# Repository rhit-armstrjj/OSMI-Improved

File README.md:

# OSMI-FinalPCB
This is a KiCad 7.0 project. You can install KiCad on Windows with:
1. Open Powershell
2. enter: `winget install KiCad.KiCad`

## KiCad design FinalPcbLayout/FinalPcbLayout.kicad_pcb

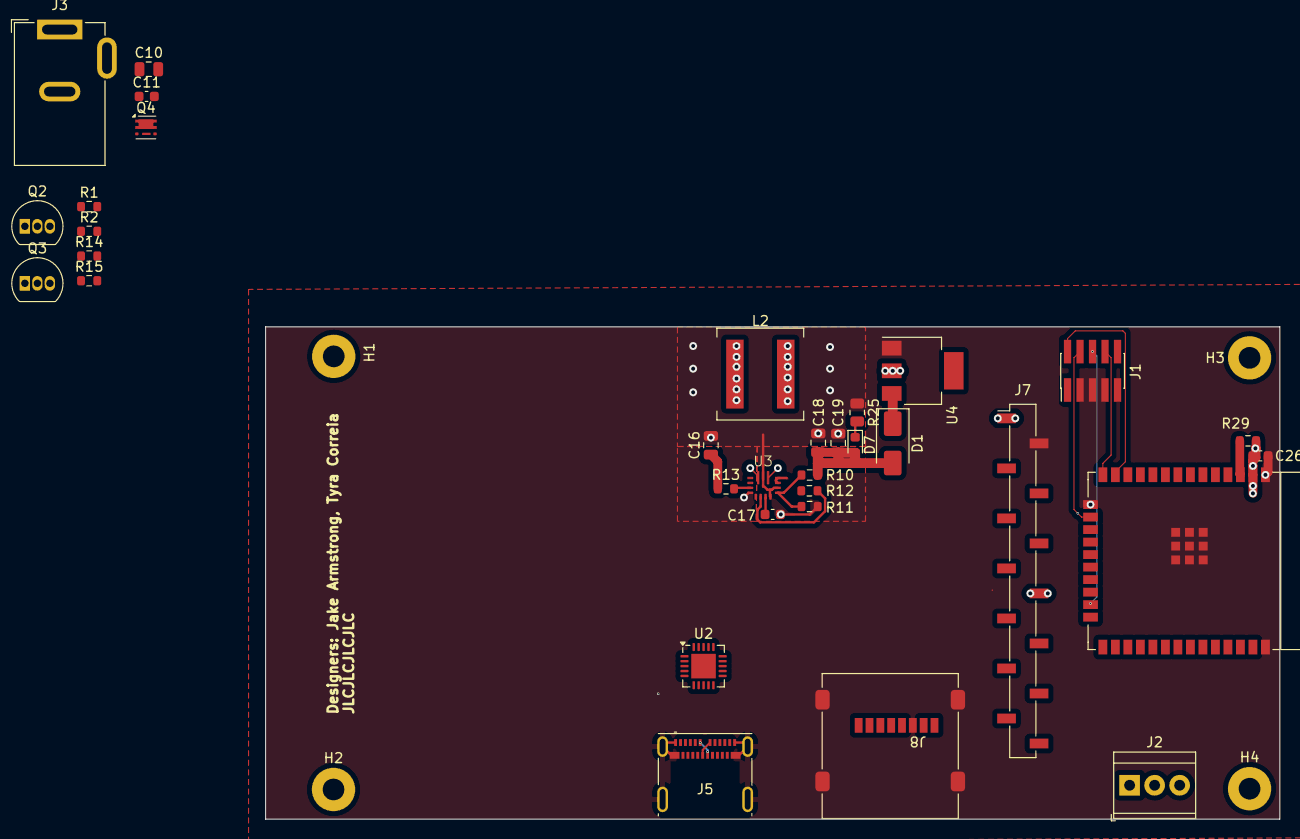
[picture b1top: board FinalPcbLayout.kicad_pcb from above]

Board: 4 copper layers, 103.0 x 50.0 mm, 37 parts (0 on the bottom side), 35 nets.

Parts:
C10, C16, C18: 10uF; C_0805_2012Metric
C11: 22uF; C_0603_1608Metric
C17: 100nF; C_0603_1608Metric
C19: 47uF; C_0805_2012Metric
C26: 0.1uF; C_0603_1608Metric
D1: D_Schottky; D_SMA
D7: RED; LED_0603_1608Metric
H1, H2, H3, H4: MountingHole; MountingHole_2.2mm_M2_Pad
J1: JTAG; PinHeader_2x05_P1.27mm_Vertical_SMD
J2: Conn_01x10; TerminalBlock_TE_282834-3_1x03_P2.54mm_Horizontal
J3: Barrel_Jack; BarrelJack_GCT_DCJ200-10-A_Horizontal
J5: USB_C_Receptacle; USB_C_Receptacle_Molex_105450-0101
J7: Display Socket; PinSocket_1x14_P2.54mm_Vertical_SMD_Pin1Left
J8: Micro_SD_Card; microSD_HC_Molex_47219-2001
L2: 2.2uH; L_Coilcraft_XAL8080-XXX
Q2, Q3: S8050; TO-92_Inline
Q4: PMOS; Vishay_PowerPAK_SC70-6L_Single
R1, R2: 5.1k 20%; R_0603_1608Metric
R10: 523k; R_0603_1608Metric
R11, R12: 100k; R_0603_1608Metric
R13, R14, R15, R29: 10k 1%; R_0603_1608Metric
R25: 100; R_0805_2012Metric
U1: ESP32-WROOM-E; ESP32-WROOM-32E
U2: FT231XQ; QFN-20-1EP_4x4mm_P0.5mm_EP2.5x2.5mm
U3: TPS63070RNMR; VQFN-15-1EP-2.5x3mm_P0.5mm
U4: LDI1117-3.3H; SOT-223

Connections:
+3.3V: C11.1, C26.1, J1.1, J7.1, J7.8, J8.4 (VDD), R29.2, U1.2 (3V3), U4.2 (VO)
+5V: C10.1, C18.1, C19.1, D1.2 (A), D7.2 (A), R10.1, R12.1, U3.7 (VOUT), U3.8 (VOUT)
+12V: C16.1, J2.1, J3.1, Q4.4 (S), R13.1, U3.1 (PS/SYNC), U3.12 (VIN), U3.13 (VIN)
/CIPO: J2.3, J7.13, J8.7 (DAT0), U1.31 (GPIO19)
/COPI: J2.2, J7.6, J7.12, J8.3 (CMD), U1.37 (GPIO23)
/Display_CS: J7.3, U1.27 (GPIO16)
/Display_DC: J7.5, U1.26 (ADC2_CH0/GPIO4)
/Display_RST: J7.4, U1.24 (ADC2_CH2/GPIO2)
/ESP_EN: Q2.3 (C), R29.1, U1.3 (EN/CHIP_PU)
/ESP_IO0_B: Q3.3 (C), U1.25 (GPIO0/BOOT/ADC2_CH1)
/JTAG_TCK: J1.4, U1.16 (MTCK/GPIO13/ADC2_CH4)
/JTAG_TDI: J1.8, U1.14 (MTDI/GPIO12/ADC2_CH5)
/JTAG_TDO: J1.6, U1.23 (MTDO/GPIO15/ADC2_CH3)
/JTAG_TMS: J1.2, U1.13 (MTMS/GPIO14/ADC2_CH6)
/Power/D1-U4: D1.1 (K), U4.3 (VI)
/Power/USB_Vin: J5.A4 (VBUS), J5.A9 (VBUS), J5.B4 (VBUS), J5.B9 (VBUS), Q4.1 (D)
/SCLK: J7.7, J7.10, J8.5 (CLK), U1.30 (GPIO18)
/SD_CS: J8.2 (DAT3/CD), U1.9 (32K_XN/GPIO33/ADC1_CH5)
/Touch_CS: J7.11, U1.29 (GPIO5)
/usb/D+: J5.A6 (D+), J5.B6 (D+)
/usb/D-: J5.A7 (D-), J5.B7 (D-)
/usb/DTR: Q3.1 (E), R15.1
/usb/RTS: Q2.1 (E), R14.1
GND: C10.2, C11.2, C16.2, C17.2, C18.2, C19.2, C26.2, J1.3, J1.5, J1.7, J1.9, J3.2, J5.A1 (GND), J5.A12 (GND), J5.B1 (GND), J5.B12 (GND), J5.S1 (SHIELD), J7.2, J8.6 (VSS), J8.9 (SHIELD), Q4.3 (G), R1.2, R2.2, R11.2, R25.2, U1.1 (GND), U1.15 (GND), U1.38 (GND), U1.39 (GND_THERMAL), U3.4 (GND), U3.6 (FB2), U3.10 (PGND), U3.15 (VSEL), U4.1 (GND)
unnamed: D7.1 (K), R25.1
unnamed: J5.A5 (CC1), R2.1
unnamed: J5.B5 (CC2), R1.1
unnamed: Q2.2 (B), R15.2
unnamed: Q3.2 (B), R14.2
unnamed: R13.2, U3.14 (EN)
unnamed: R10.2, R11.1, U3.5 (FB)
unnamed: L2.1, U3.11 (L1)
unnamed: L2.2, U3.9 (L2)
unnamed: R12.2, U3.2 (PG)
unnamed: C17.1, U3.3 (VAUX)

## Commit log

2024-01-17 cool
2024-01-19 MORE PCB
2024-01-19 sound chip done
2024-01-19 QFN_2.5x3mm Footprint
2024-01-19 VQFN Footprint Traces Laid Out
2024-01-19 Solder Mask Completed
2024-01-19 Removed Lock
2024-01-19 Zip Updated
2024-01-22 USB PD Device Symbol
2024-01-22 beep
2024-01-22 Symbol Completed
2024-01-22 slay
2024-01-22 USB Autoprogramming
2024-01-22 broski
2024-01-22 VCORE Connections
2024-01-22 More USB PD
2024-01-22 for jake
2024-01-22 Updated Footprints
2024-01-22 route some gnd
2024-01-23 Added Diode Model
2024-01-23 power supplies
2024-01-23 pOWER DONE
2024-01-23 Tyra's work is done here
2024-01-23 USB Layout w/ EEPROM
2024-01-23 Part Finalization
2024-01-23 Sim Disabled
2024-01-23 Added Footprint to NPN Transistors
2024-01-23 Update schematic with footprints for power delivery
2024-01-24 No ERC Errors
2024-01-24 All changes imported to PCB
2024-01-24 Routed UART Bridge
2024-01-24 Final Pcb Routed (without headers)
2024-01-24 Added VOut Rails
2024-01-24 Removed Locks
2024-01-24 Generated CSV
2024-01-24 One More Check
2024-01-24 Fixed Resistance
2024-01-25 More Schematic Label Updates
2024-01-25 Added drawings.
    Marginal layout changes. Does not affect board design. See tagged revision for what was sent to the board house.
2024-01-25 Fixed Wrong Resistor
2024-01-26 Opened And Closed
2024-02-10 Updated CSV
2024-02-18 Generated Bill of Materials
2024-02-18 Moved interactive bill of materials
2024-04-17 Changes from February
2024-04-17 Axed Several Broken & Unused Parts
2024-04-17 Found A Good USB-To-Uart
2024-05-26 Working on USB to UART
2024-06-10 adv channel control
